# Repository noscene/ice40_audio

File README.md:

# ice40_audio
verilog example to drive PCM5102 DAC with FPGA

Using:
- PCM5102 from eBay
- iceZero from trenz-electronic.de
- ice storm open source tool chain

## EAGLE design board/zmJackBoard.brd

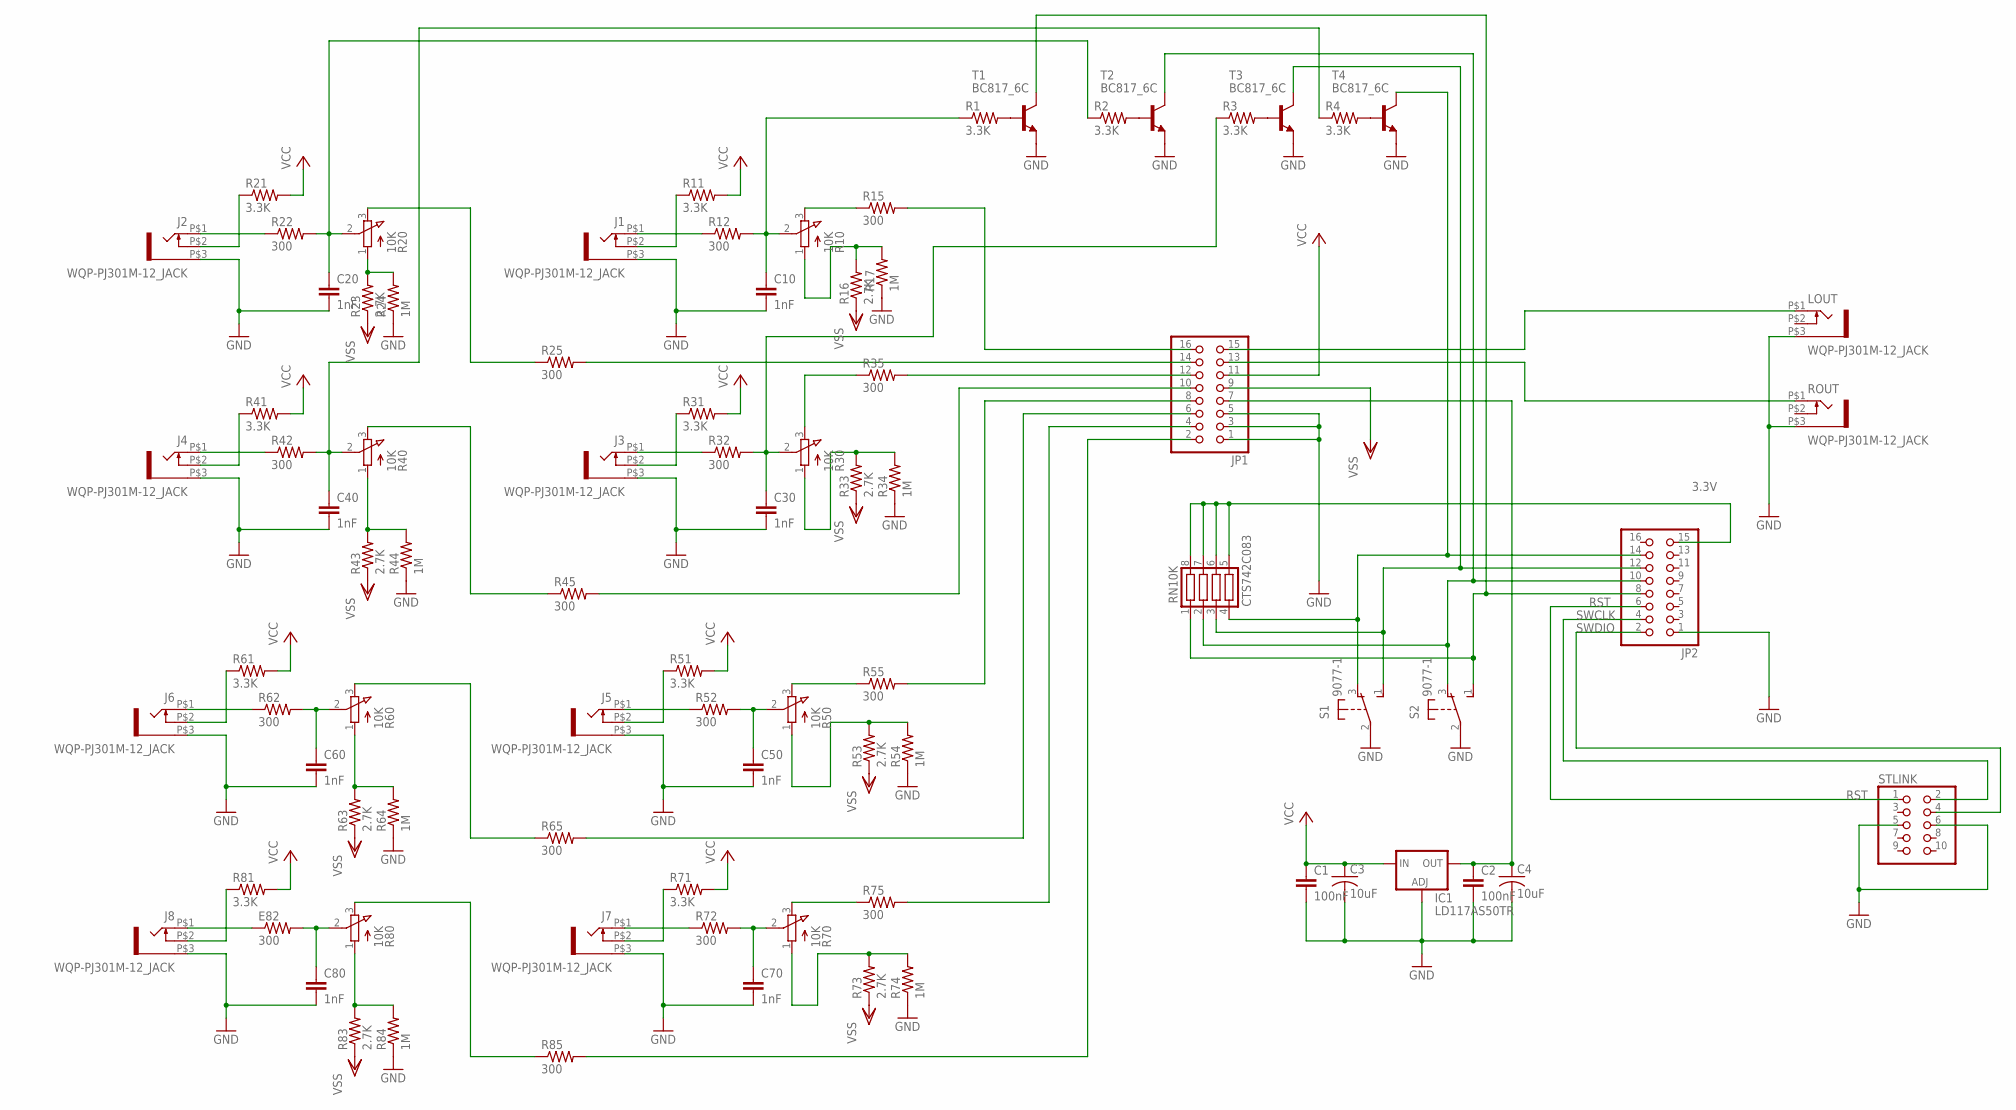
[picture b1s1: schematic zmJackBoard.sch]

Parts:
C1, C2: 100nF; C0805
C3, C4: 10uF; C1206
C10, C20, C30, C40, C50, C60, C70, C80: 1nF; C0805
E82: 300; M0805
IC1: LD117AS50TR; SOT223
J1, J2, J3, J4, J5, J6, J7, J8: WQP-PJ301M-12_JACK
JP1, JP2: PINHD-2X8; 2X08
LOUT: WQP-PJ301M-12_JACK
R1, R2, R3, R4, R11, R21, R31, R41, R51, R61, R71, R81: 3.3K; M0805
R10, R20, R30, R40, R50, R60, R70, R80: 10K; EVUFXL
R12, R15, R22, R25, R32, R35, R42, R45, R52, R55, R62, R65, R72, R75, R85: 300; M0805
R16, R23, R33, R43, R53, R63, R73, R83: 2.7K; M0805
R17, R24, R34, R44, R54, R64, R74, R84: 1M; M0805
RN10K: CTS742C083
ROUT: WQP-PJ301M-12_JACK
S1, S2: 9077-1
STLINK: PINHD-2X5; 2X05
T1, T2, T3, T4: BC817_6C; SOT23-EBC

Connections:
3.3V: JP2.15, RN10K.5, RN10K.6, RN10K.7, RN10K.8
5V: C2.1, C4.1, IC1.4 (OUT), JP1.7
ADC1: JP1.16, R15.2
ADC2: JP1.14, R25.2
ADC3: JP1.12, R35.2
ADC4: JP1.10, R45.2
ADC5: JP1.8, R55.2
ADC6: JP1.6, R65.2
ADC7: JP1.4, R75.2
ADC8: JP1.2, R85.2
GND: C1.2, C2.2, C3.2, C4.2, C10.2, C20.2, C30.2, C40.2, C50.2, C60.2, C70.2, C80.2, IC1.1 (ADJ), J1.P$3 (1), J2.P$3 (1), J3.P$3 (1), J4.P$3 (1), J5.P$3 (1), J6.P$3 (1), J7.P$3 (1), J8.P$3 (1), JP1.1, JP1.3, JP1.5, JP2.1, LOUT.P$3 (1), R17.1, R24.1, R34.1, R44.1, R54.1, R64.1, R74.1, R84.1, ROUT.P$3 (1), S1.2, S2.2, STLINK.5, STLINK.6, T1.E, T2.E, T3.E, T4.E
LOUT: JP1.15, LOUT.P$1 (2)
unnamed: J2.P$1 (2), R22.1
unnamed: R30.3 (E), R35.1
unnamed: J2.P$2 (3), R21.1
unnamed: C20.1, R2.1, R20.2 (S), R22.2
unnamed: J1.P$2 (3), R11.1
unnamed: J4.P$2 (3), R41.1
unnamed: J4.P$1 (2), R42.1
unnamed: C40.1, R4.1, R40.2 (S), R42.2
unnamed: J1.P$1 (2), R12.1
unnamed: J6.P$2 (3), R61.1
unnamed: J6.P$1 (2), R62.1
unnamed: C60.1, R60.2 (S), R62.2
unnamed: C10.1, R1.1, R10.2 (S), R12.2
unnamed: J8.P$2 (3), R81.1
unnamed: E82.1, J8.P$1 (2)
unnamed: C80.1, E82.2, R80.2 (S)
unnamed: J3.P$2 (3), R31.1
unnamed: J3.P$1 (2), R32.1
unnamed: C30.1, R3.1, R30.2 (S), R32.2
unnamed: J5.P$2 (3), R51.1
unnamed: J5.P$1 (2), R52.1
unnamed: C50.1, R50.2 (S), R52.2
unnamed: J7.P$2 (3), R71.1
unnamed: J7.P$1 (2), R72.1
unnamed: C70.1, R70.2 (S), R72.2
unnamed: JP2.8, RN10K.1, S2.1 (S), T1.C
unnamed: JP2.10, RN10K.2, S2.3 (O), T2.C
unnamed: JP2.12, RN10K.3, S1.1 (S), T3.C
unnamed: JP2.14, RN10K.4, S1.3 (O), T4.C
unnamed: R1.2, T1.B
unnamed: R2.2, T2.B
unnamed: R3.2, T3.B
unnamed: R4.2, T4.B
unnamed: R40.3 (E), R45.1
unnamed: R20.3 (E), R25.1
unnamed: R60.3 (E), R65.1
unnamed: R80.3 (E), R85.1
unnamed: R10.3 (E), R15.1
unnamed: R50.3 (E), R55.1
unnamed: R70.3 (E), R75.1
unnamed: R10.1 (A), R16.2, R17.2
unnamed: R80.1 (A), R83.2, R84.2
unnamed: R60.1 (A), R63.2, R64.2
unnamed: R40.1 (A), R43.2, R44.2
unnamed: R20.1 (A), R23.2, R24.2
unnamed: R30.1 (A), R33.2, R34.2
unnamed: R50.1 (A), R53.2, R54.2
unnamed: R70.1 (A), R73.2, R74.2
ROUT: JP1.13, ROUT.P$1 (2)
RST: JP2.6, STLINK.1
SWCLK: JP2.4, STLINK.2
SWDIO: JP2.2, STLINK.4
VCC: C1.1, C3.1, IC1.3 (IN), JP1.11, R11.2, R21.2, R31.2, R41.2, R51.2, R61.2, R71.2, R81.2
VSS: JP1.9, R16.1, R23.1, R33.1, R43.1, R53.1, R63.1, R73.1, R83.1

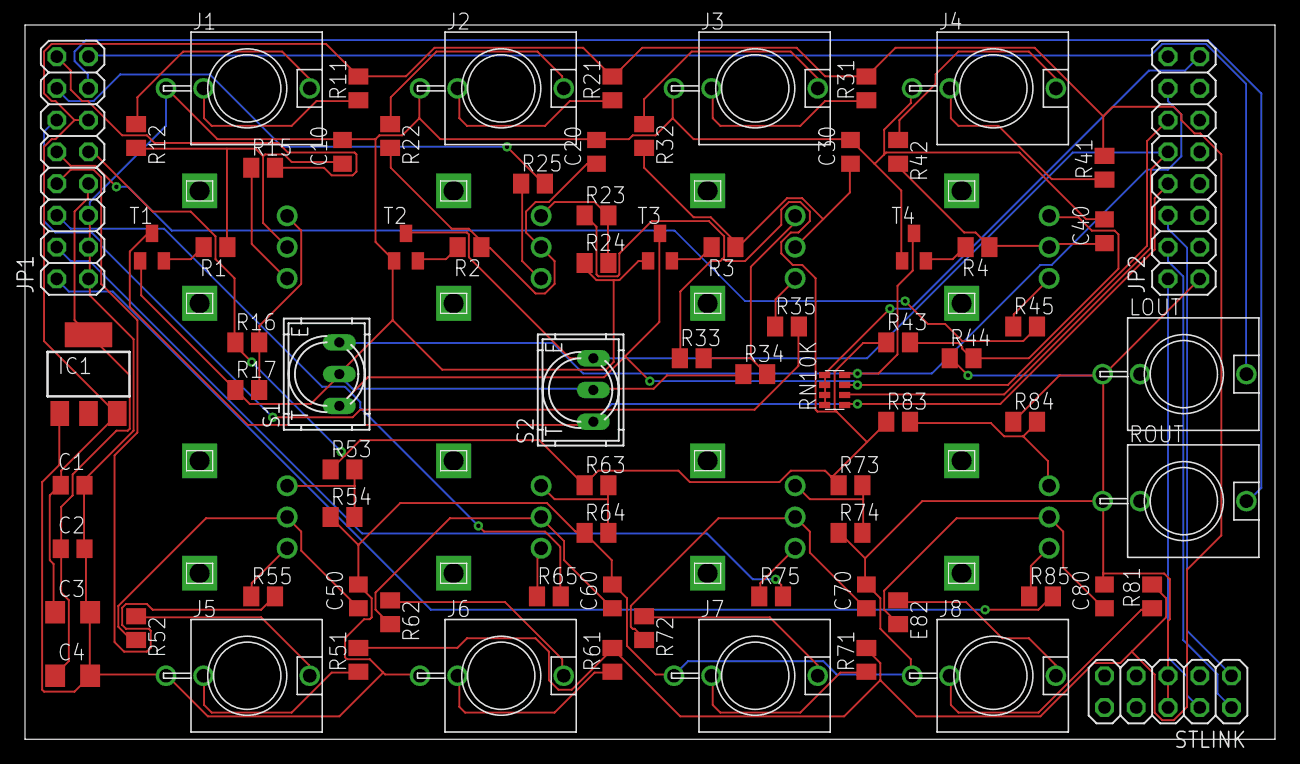
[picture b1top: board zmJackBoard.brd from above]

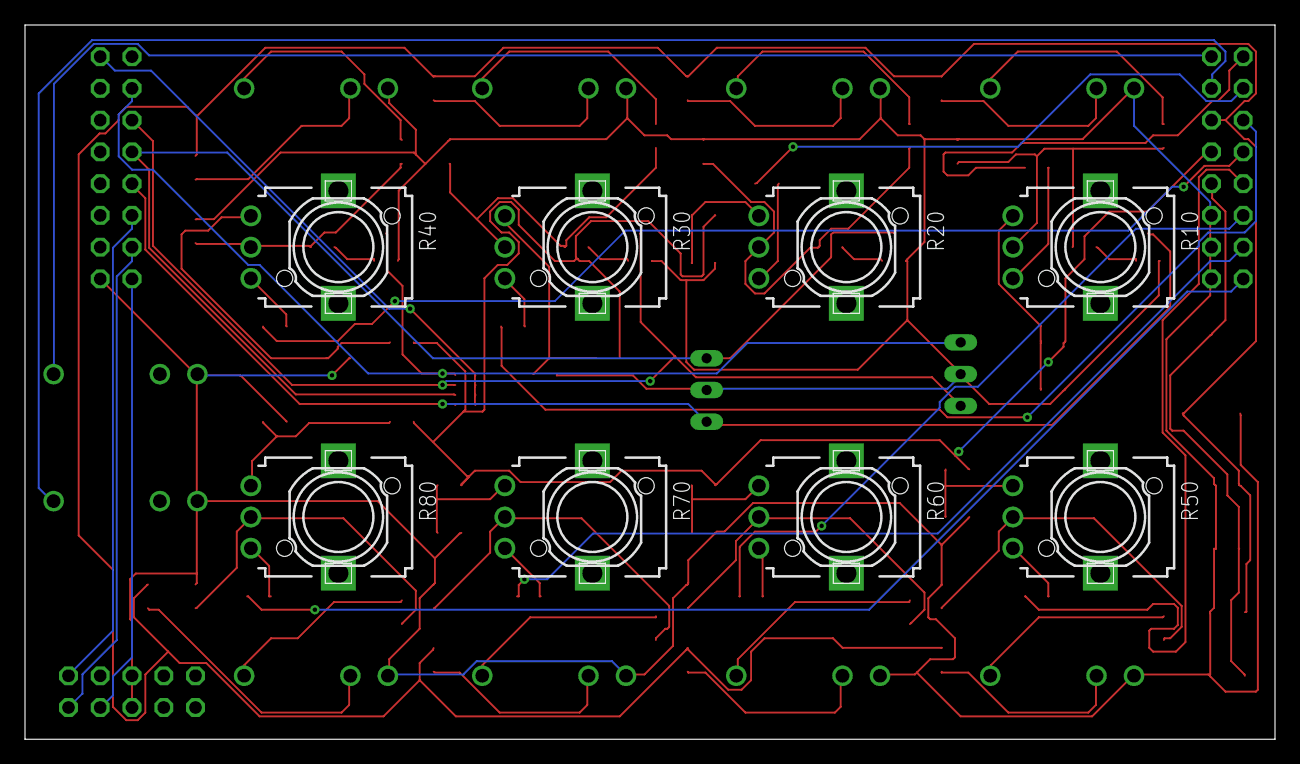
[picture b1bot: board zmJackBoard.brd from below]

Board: 2 copper layers, 100.0 x 57.1 mm, 85 parts (8 on the bottom side), 66 nets.

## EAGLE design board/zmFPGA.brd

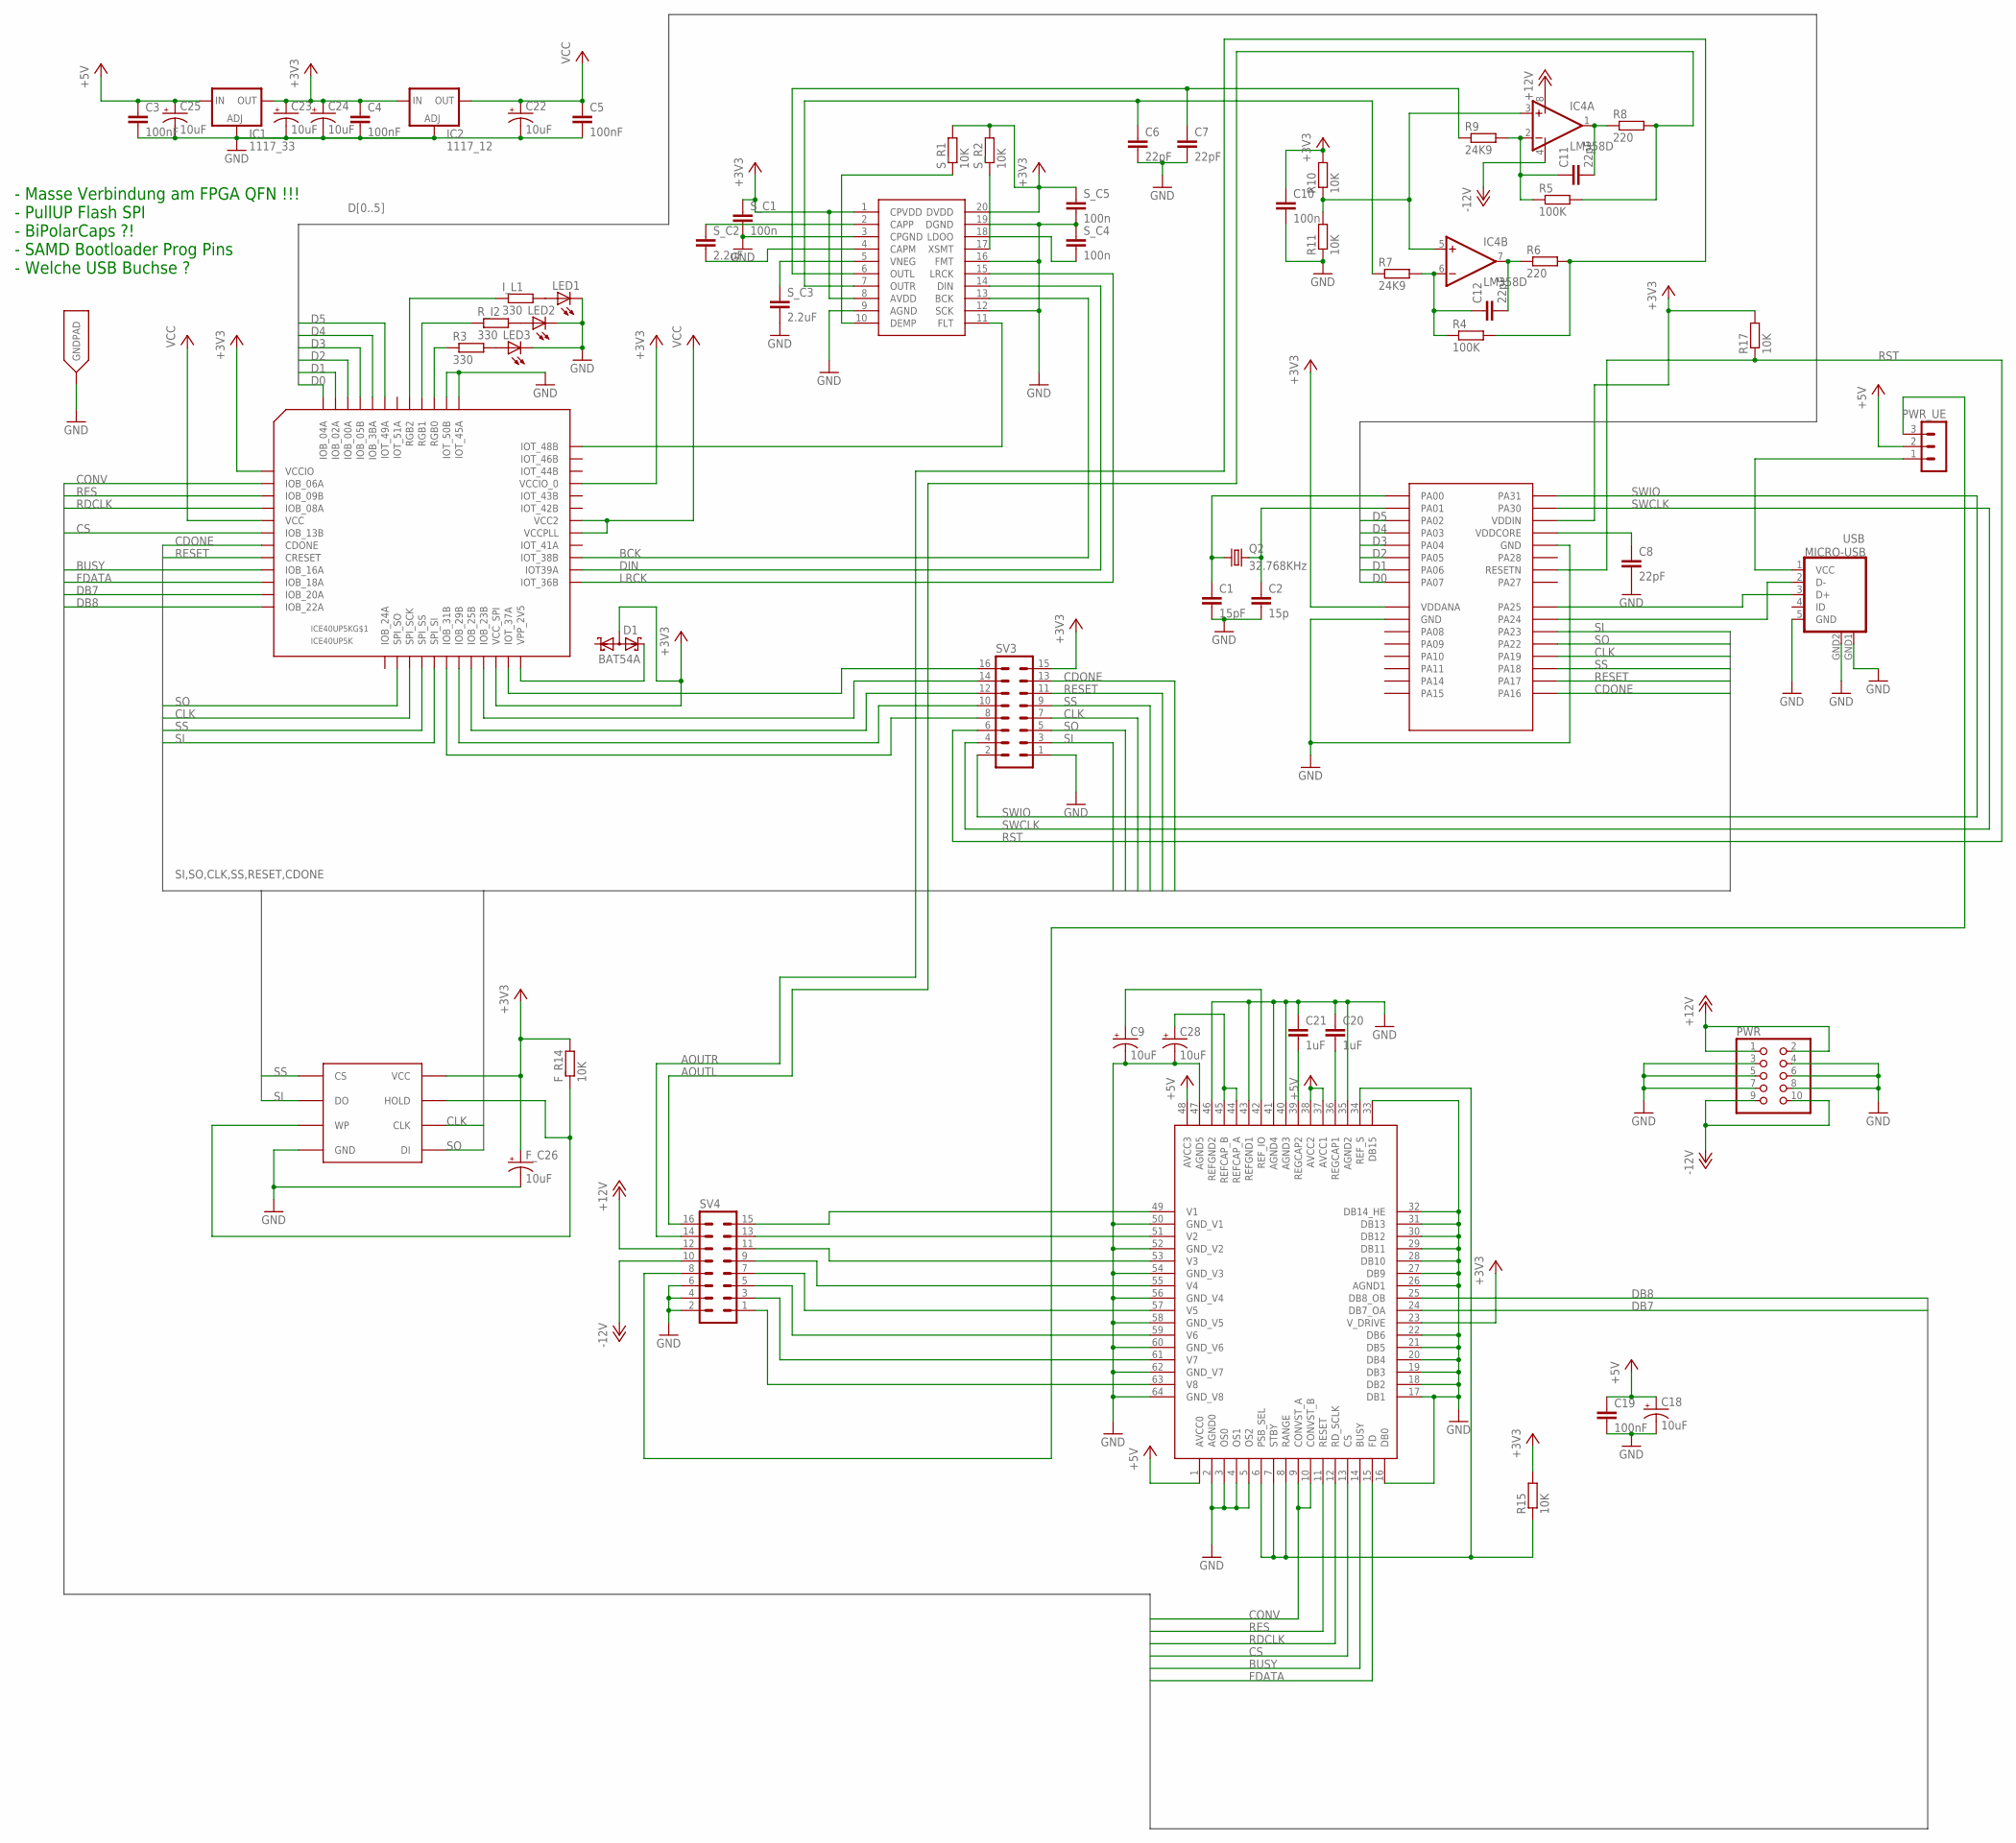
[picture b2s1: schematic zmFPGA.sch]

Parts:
AD7606: AD7606; LQFP64
C1: 15pF; C0805
C2: 15p; C0805
C3, C4, C5, C19: 100nF; C0805
C6, C7, C8, C11, C12: 22pF; C0805
C9, C18, C22, C23, C24, C25, C28: 10uF; EIA3216
C10: 100n; C0805
C20, C21: 1uF; C0805
D1: BAT54A; SOT23
F_C26: 10uF; EIA3216
F_R14: 10K; R0805
IC1: 1117_33; SOT223
IC2: 1117_12; SOT223
IC4: LM358D; SO08
ICE40UP5K: ICE40UP5K; QFN48
I_L1: 330; R0805
LED1, LED2, LED3: LEDSMT1206; 1206
PCM5102: PCM5102; TSSOP20
PWR: PINHD-2X5; 2X05
PWR_UE: MA03-1
Q2: 32.768KHz; MM39SL
R3: 330; R0805
R4, R5: 100K; R0805
R6, R8: 220; R0805
R7, R9: 24K9; R0805
R10, R11, R15: 10K; R0805
R17: 10K; R1206
R_I2: 330; R0805
SV3, SV4: MA08-2
S_C1, S_C4, S_C5: 100n; C0805
S_C2, S_C3: 2.2uF; C0805
S_R1, S_R2: 10K; R0805
U$1: W25Q32; SOP-8
U$2: SAMD21_TQFP32; 32-TQFP
USB: MICRO-USB

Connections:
5VEXT: PWR_UE.3, SV4.8
+3V3: AD7606.23 (V_DRIVE), C4.1, C10.1, C23.+, C24.+, D1.3 (AA), F_C26.+, F_R14.2, IC1.4 (OUT), IC2.3 (IN), ICE40UP5K.1 (VCCIO), ICE40UP5K.22 (VCC_SPI), ICE40UP5K.33 (VCCIO_0), PCM5102.1 (CPVDD), PCM5102.8 (AVDD), PCM5102.20 (DVDD), R10.2, R15.2, R17.2, SV3.15, S_C1.1, S_C5.1, S_R1.2, S_R2.2, U$1.8 (VCC), U$2.9 (VDDANA), U$2.30 (VDDIN)
+5V: AD7606.1 (AVCC0), AD7606.37 (AVCC1), AD7606.38 (AVCC2), AD7606.48 (AVCC3), C3.1, C18.+, C19.1, C25.+, IC1.3 (IN), PWR_UE.2
+12V: IC4.8 (V+), PWR.1, PWR.2, SV4.12
-12V: IC4.4 (V-), PWR.9, PWR.10, SV4.10
AOUTL: R5.2, R8.2, SV4.16
AOUTR: R4.2, R6.2, SV4.14
B23: ICE40UP5K.21 (IOB_23B), SV3.14
B25: ICE40UP5K.20 (IOB_25B), SV3.12
B29: ICE40UP5K.19 (IOB_29B), SV3.10
B31: ICE40UP5K.18 (IOB_31B), SV3.8
BCK: ICE40UP5K.27 (IOT_38B), PCM5102.13 (BCK)
BUSY: AD7606.14 (BUSY), ICE40UP5K.9 (IOB_16A)
CAPM: PCM5102.4 (CAPM), S_C2.2
CAPP: PCM5102.2 (CAPP), S_C2.1
CDONE: ICE40UP5K.7 (CDONE), SV3.13, U$2.17 (PA16)
CLK: ICE40UP5K.15 (SPI_SCK), SV3.7, U$1.6 (CLK), U$2.20 (PA19)
CONV: AD7606.9 (CONVST_A), AD7606.10 (CONVST_B), ICE40UP5K.2 (IOB_06A)
CS: AD7606.13 (CS), ICE40UP5K.6 (IOB_13B)
D0: ICE40UP5K.48 (IOB_04A), U$2.8 (PA07)
D1: ICE40UP5K.47 (IOB_02A), U$2.7 (PA06)
D2: ICE40UP5K.46 (IOB_00A), U$2.6 (PA05)
D3: ICE40UP5K.45 (IOB_05B), U$2.5 (PA04)
D4: ICE40UP5K.44 (IOB_3BA), U$2.4 (PA03)
D5: ICE40UP5K.43 (IOT_49A), U$2.3 (PA02)
D+: U$2.24 (PA25), USB.3 (D+)
D-: U$2.23 (PA24), USB.2 (D-)
DB7: AD7606.24 (DB7_OA), ICE40UP5K.11 (IOB_20A)
DB8: AD7606.25 (DB8_OB), ICE40UP5K.12 (IOB_22A)
DIN: ICE40UP5K.26 (IOT39A), PCM5102.14 (DIN)
FDATA: AD7606.15 (FD), ICE40UP5K.10 (IOB_18A)
FLASH_H: F_R14.1, U$1.3 (WP), U$1.7 (HOLD)
FLT: ICE40UP5K.36 (IOT_48B), PCM5102.11 (FLT)
GND: AD7606.2 (AGND0), AD7606.3 (OS0), AD7606.4 (OS1), AD7606.5 (OS2), AD7606.16 (DB0), AD7606.17 (DB1), AD7606.18 (DB2), AD7606.19 (DB3), AD7606.20 (DB4), AD7606.21 (DB5), AD7606.22 (DB6), AD7606.26 (AGND1), AD7606.27 (DB9), AD7606.28 (DB10), AD7606.29 (DB11), AD7606.30 (DB12), AD7606.31 (DB13), AD7606.32 (DB14_HE), AD7606.33 (DB15), AD7606.35 (AGND2), AD7606.40 (AGND3), AD7606.41 (AGND4), AD7606.43 (REFGND1), AD7606.46 (REFGND2), AD7606.47 (AGND5), AD7606.50 (GND_V1), AD7606.52 (GND_V2), AD7606.54 (GND_V3), AD7606.56 (GND_V4), AD7606.58 (GND_V5), AD7606.60 (GND_V6), AD7606.62 (GND_V7), AD7606.64 (GND_V8), C1.2, C2.2, C3.2, C4.2, C5.2, C6.2, C7.2, C8.2, C9.-, C10.2, C18.-, C19.2, C20.1, C21.1, C22.-, C23.-, C24.-, C25.-, C28.-, F_C26.-, IC1.1 (ADJ), IC2.1 (ADJ), ICE40UP5K.37 (IOT_45A), ICE40UP5K.38 (IOT_50B), ICE40UP5K.EXP (GNDPAD), LED1.C, LED2.C, LED3.C, PCM5102.3 (CPGND), PCM5102.9 (AGND), PCM5102.12 (SCK), PCM5102.16 (FMT), PCM5102.19 (DGND), PWR.3, PWR.4, PWR.5, PWR.6, PWR.7, PWR.8, R11.1, SV3.1, SV4.2, SV4.4, SV4.6, S_C1.2, S_C3.2, S_C4.1, S_C5.2, U$1.4 (GND), U$2.10 (GND), U$2.28 (GND), USB.5 (GND), USB.GND1 (GND), USB.GND2 (GND)
LRCK: ICE40UP5K.25 (IOT_36B), PCM5102.15 (LRCK)
unnamed: C8.1, U$2.29 (VDDCORE)
unnamed: AD7606.63 (V8), SV4.1
unnamed: AD7606.61 (V7), SV4.3
unnamed: AD7606.59 (V6), SV4.5
unnamed: D1.2 (K2), ICE40UP5K.24 (VPP_2V5)
unnamed: AD7606.57 (V5), SV4.7
unnamed: AD7606.55 (V4), SV4.9
unnamed: AD7606.53 (V3), SV4.11
unnamed: AD7606.51 (V2), SV4.13
unnamed: LED3.A, R3.2
unnamed: LED2.A, R_I2.2
unnamed: I_L1.2, LED1.A
unnamed: ICE40UP5K.39 (RGB0), R3.1
unnamed: ICE40UP5K.40 (RGB1), R_I2.1
unnamed: ICE40UP5K.41 (RGB2), I_L1.1
unnamed: C12.2, IC4.7 (OUT), R6.1
unnamed: C11.2, IC4.1 (OUT), R8.1
unnamed: C11.1, IC4.2 (-IN), R5.1, R9.2
unnamed: C12.1, IC4.6 (-IN), R4.1, R7.2
unnamed: PCM5102.17 (XSMT), S_R2.1
unnamed: PCM5102.10 (DEMP), S_R1.1
unnamed: PCM5102.18 (LDOO), S_C4.2
unnamed: AD7606.49 (V1), SV4.15
OUTL: C7.1, PCM5102.6 (OUTL), R9.1
OUTR: C6.1, PCM5102.7 (OUTR), R7.1
PULLUP: AD7606.6 (PSB_SEL), AD7606.7 (STBY), AD7606.8 (RANGE), AD7606.34 (REF_S), R15.1
Q1: C1.1, Q2.1, U$2.1 (PA00)
Q2: C2.1, Q2.4 (2), U$2.2 (PA01)
RDCLK: AD7606.12 (RD_SCLK), ICE40UP5K.4 (IOB_08A)
REFCAP: AD7606.44 (REFCAP_A), AD7606.45 (REFCAP_B), C28.+
REF_INOUT: AD7606.42 (REF_IO), C9.+
REGCAP1: AD7606.36 (REGCAP1), C20.2
REGCAP2: AD7606.39 (REGCAP2), C21.2
RES: AD7606.11 (RESET), ICE40UP5K.3 (IOB_09B)
RESET: ICE40UP5K.8 (CRESET), SV3.11, U$2.18 (PA17)
RST: R17.1, SV3.6, U$2.26 (RESETN)
SI: ICE40UP5K.17 (SPI_SI), SV3.3, U$1.2 (DO), U$2.22 (PA23)
SO: ICE40UP5K.14 (SPI_SO), SV3.5, U$1.5 (DI), U$2.21 (PA22)
SS: ICE40UP5K.16 (SPI_SS), SV3.9, U$1.1 (CS), U$2.19 (PA18)
SWCLK: SV3.4, U$2.31 (PA30)
SWIO: SV3.2, U$2.32 (PA31)
T37: ICE40UP5K.23 (IOT_37A), SV3.16
USB_5V: PWR_UE.1, USB.1 (VCC)
V165: IC4.3 (+IN), IC4.5 (+IN), R10.1, R11.2
VCC: C5.1, C22.+, IC2.4 (OUT), ICE40UP5K.5 (VCC), ICE40UP5K.29 (VCCPLL), ICE40UP5K.30 (VCC2)
VNEG: PCM5102.5 (VNEG), S_C3.1

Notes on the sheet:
- Masse Verbindung am FPGA QFN !!! - PullUP Flash SPI - BiPolarCaps ?! - SAMD Bootloader Prog Pins - Welche USB Buchse ?

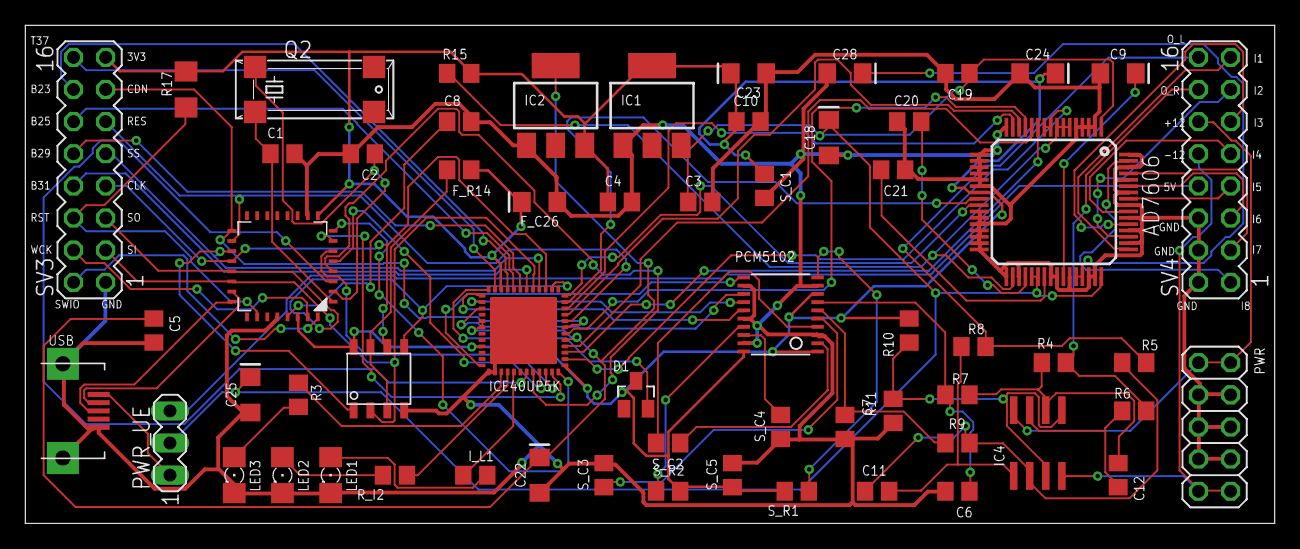
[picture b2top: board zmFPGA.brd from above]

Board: 2 copper layers, 98.7 x 39.4 mm, 61 parts (0 on the bottom side), 81 nets.

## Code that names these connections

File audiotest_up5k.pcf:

set_io LED1 39
set_io LED2 40
set_io LED3 41
set_io pa07 43 
set_io clk 4


set_io  LRCK 	25
set_io  DIN	26
set_io	BCK	27

set_io	AD_CONV		2
set_io	AD_RESET	3
set_io	AD_RDCLK	4
set_io	AD_CS		6
set_io	AD_BUSY		9
set_io	AD_FDATA   10
set_io	AD_DB7	   11
set_io	AD_DB8	   12

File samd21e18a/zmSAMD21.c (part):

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
    SERCOM1->SPI.BAUD.reg = 0; // Rate is clock / 2 

    // Mux for SERCOM1 PA16,PA17,PA18,PA19
    const PORT_WRCONFIG_Type wrconfig = {
      .bit.WRPINCFG = 1,
      .bit.WRPMUX = 1,
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
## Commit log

2018-02-06 init
2018-02-06 some info
2018-02-13 - add simple additive synth - switch from cordic to sysram/bram lookup - save around 2000luts on ice40
2018-03-02 - add board v0.1 (first design)
2018-03-04 -add Dockerfile to fast build toolchain # build with docker build -t icestorm icestorm/ # run toolchain and mount Mac Volume docker run -it -v ~/Desktop:/Desktop icestorm bash
2018-03-11 -add first firmware test for samd21e18
2018-03-23 - implement 8 channel dac AD7606 - simple additive oscillator + vca - optimize makefile for debugging - switch to ice40up5k
2018-03-27 - test additive synth with cordic - restruct modules
2018-03-29 - add noise gen module
2018-04-06 - add gate2trigger module - add supersaw module - fix decay
2018-04-08 - add tri soc - add pitch to supersaw - fix decay - add quadrant sin table 1024x16 - fix 5102 upper bit (todo: remove jitter)
2018-04-12 - add jackboard (its only for testing resistor values are not final!)
2018-04-14 - add 1/4 sin wave to fpga bram (script for makefile)
2018-04-17 - add tri + saw - fix dac output (remove R10 from pcb!)
2018-04-24 fix cll/data timing for 7606 / 7607
2018-04-24 - add samd21 header files
2018-04-30 Full oscillator unit with waveselect, pitch, amp by CV

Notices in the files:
parts and their libraries:
SparkFun-Capacitors: Licensing: Creative Commons ShareAlike 4.0 International - https://creativecommons.org/licenses/by-sa/4.0
